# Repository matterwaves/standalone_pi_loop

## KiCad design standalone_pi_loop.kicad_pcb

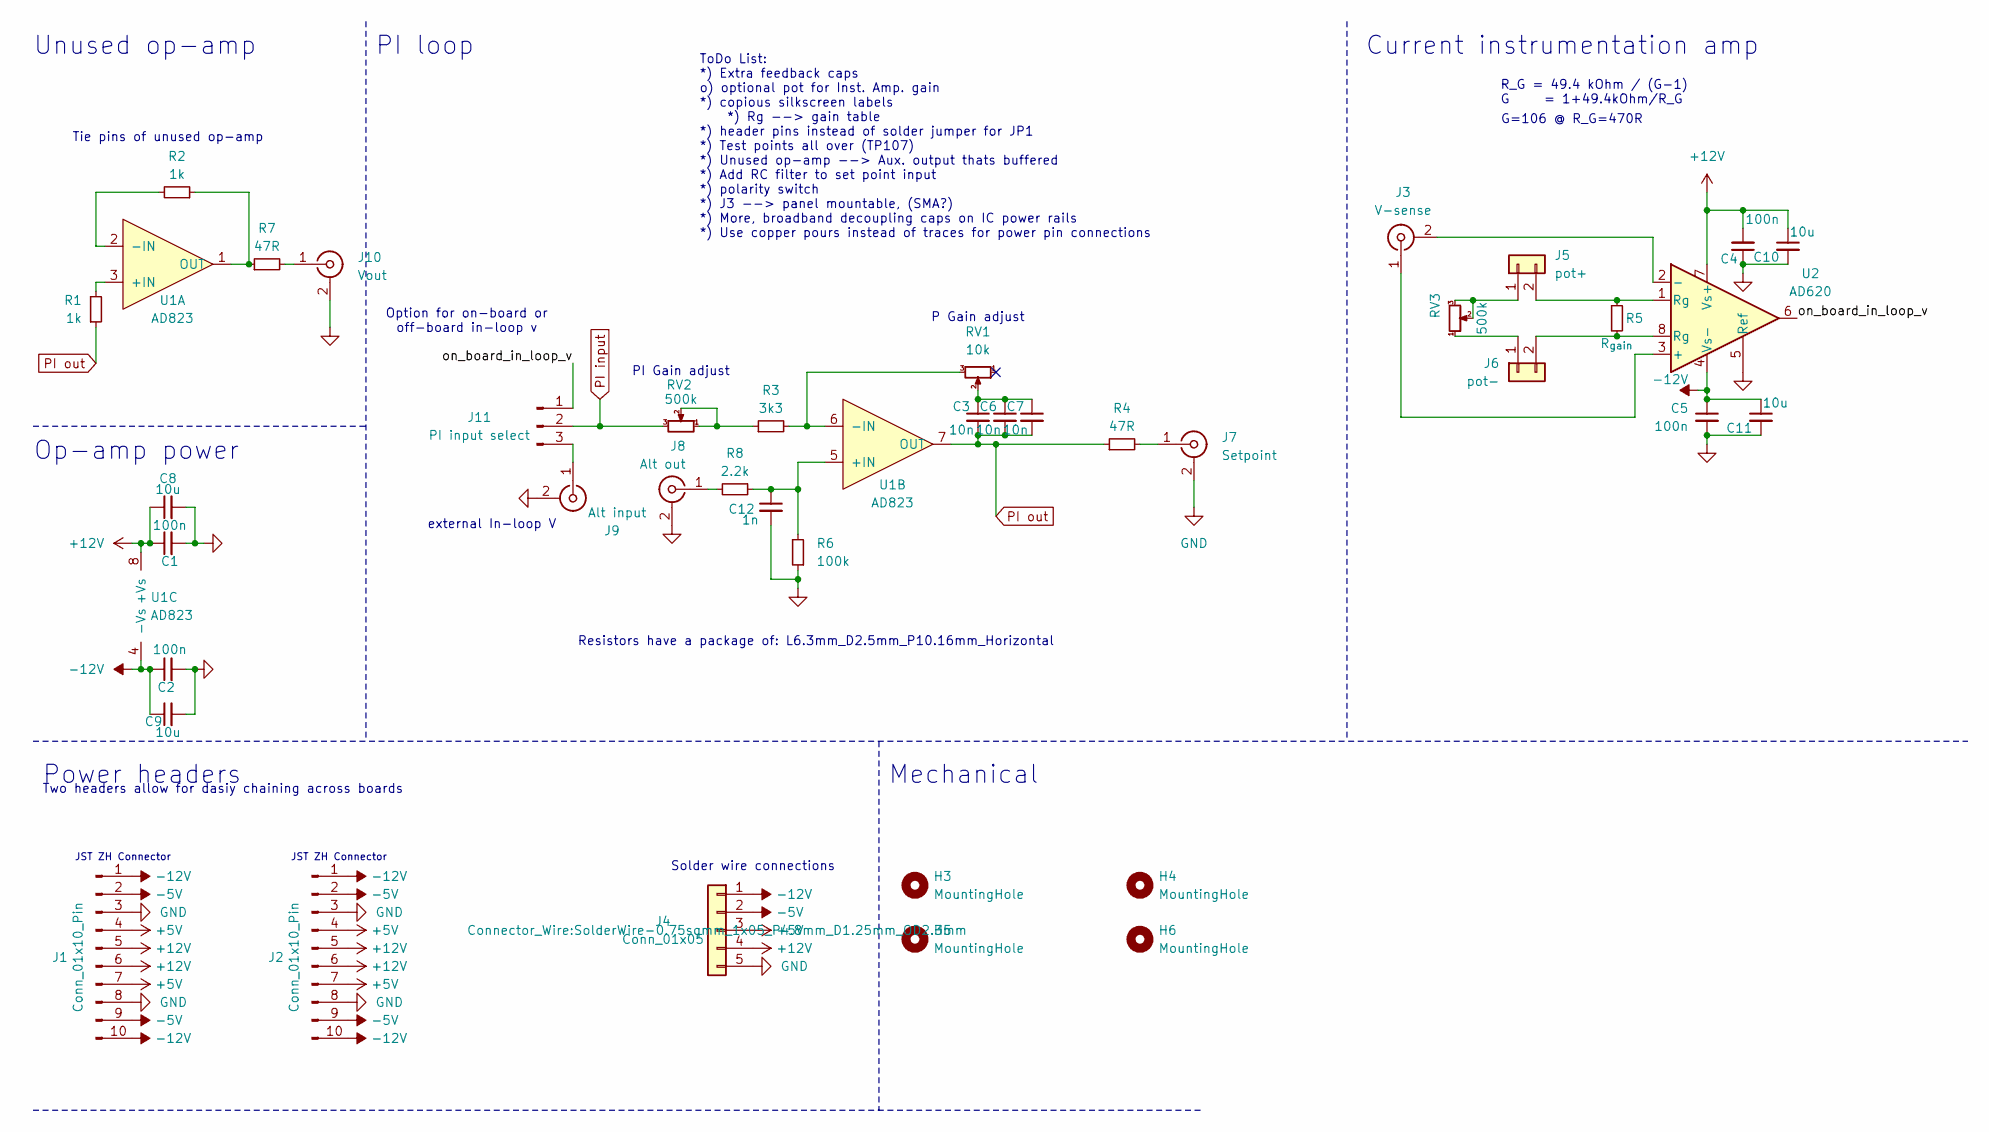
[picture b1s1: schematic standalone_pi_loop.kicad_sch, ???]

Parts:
C1, C2, C4, C5: 100n; C_Disc_D4.3mm_W1.9mm_P5.00mm
C3, C6, C7: 10n; C_Disc_D4.3mm_W1.9mm_P5.00mm
C8, C9, C10, C11: 10u; C_Disc_D4.3mm_W1.9mm_P5.00mm
C12: 1n; C_Disc_D4.3mm_W1.9mm_P5.00mm
H3, H4, H5, H6: MountingHole; MountingHole_3.2mm_M3
J1, J2: Conn_01x10_Pin; JST_ZH_B10B-ZR_1x10_P1.50mm_Vertical; Digikey PN 455-S10B-ZR-ND
J3: V-sense; SMA_Amphenol_132289_EdgeMount; Digikey PN ACX1426-ND
J4: Conn_01x05; SolderWire-0.75sqmm_1x05_P4.8mm_D1.25mm_OD2.3mm
J5: pot+; PinHeader_1x02_P2.54mm_Vertical
J6: pot-; PinHeader_1x02_P2.54mm_Vertical
J7: Setpoint; SMA_Amphenol_132289_EdgeMount; Digikey PN ACX1426-ND
J8: Alt out; SMA_Amphenol_132289_EdgeMount; Digikey PN ACX1426-ND
J9: Alt input; SMA_Amphenol_132289_EdgeMount; Digikey PN ACX1426-ND
J10: Vout; SMA_Amphenol_132289_EdgeMount; Digikey PN ACX1426-ND
J11: PI input select; PinHeader_1x03_P2.54mm_Vertical
R1, R2: 1k; R_Axial_DIN0207_L6.3mm_D2.5mm_P10.16mm_Horizontal
R3: 3k3; R_Axial_DIN0207_L6.3mm_D2.5mm_P10.16mm_Horizontal
R4, R7: 47R; R_Axial_DIN0207_L6.3mm_D2.5mm_P10.16mm_Horizontal
R5: R_{gain}; R_Axial_DIN0207_L6.3mm_D2.5mm_P10.16mm_Horizontal
R6: 100k; R_Axial_DIN0207_L6.3mm_D2.5mm_P10.16mm_Horizontal
R8: 2.2k; R_Axial_DIN0207_L6.3mm_D2.5mm_P10.16mm_Horizontal
RV1: 10k; Potentiometer_Bourns_3296W_Vertical
RV2, RV3: 500k; Potentiometer_Bourns_3296W_Vertical
U1: AD823; DIP-8_W7.62mm_Socket_LongPads
U2: AD620; DIP-8_W7.62mm_Socket_LongPads

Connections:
+5V: J1.4, J1.7, J2.4, J2.7, J4.3
+12V: C1.1, C4.2, C8.1, C10.1, J1.5, J1.6, J2.5, J2.6, J4.4, U1.8 (+Vs), U2.7 (Vs+)
-5V: J1.2, J1.9, J2.2, J2.9, J4.2
-12V: C2.1, C5.1, C9.1, C11.1, J1.1, J1.10, J2.1, J2.10, J4.1, U1.4 (-Vs), U2.4 (Vs-)
/on_board_in_loop_v: J11.1, U2.6
GND: C1.2, C2.2, C4.1, C5.2, C8.2, C9.2, C10.2, C11.2, C12.2, J1.3, J1.8, J2.3, J2.8, J4.5, J7.2 (Ext), J8.2 (Ext), J9.2 (Ext), J10.2 (Ext), R6.1, U2.5 (Ref)
unnamed: C3.1, C6.1, C7.1, RV1.2
unnamed: J3.2 (Ext), U2.2 (-)
unnamed: J3.1 (In), U2.3 (+)
unnamed: J5.1, RV3.2, RV3.3
unnamed: J5.2, R5.1, U2.1 (Rg)
unnamed: J6.1, RV3.1
unnamed: J6.2, R5.2, U2.8 (Rg)
unnamed: J7.1 (In), R4.2
unnamed: J8.1 (In), R8.2
unnamed: J10.1 (In), R7.2
unnamed: J9.1 (In), J11.3
unnamed: R3.1, RV2.1, RV2.2
unnamed: R1.2, U1.3 (+IN)
unnamed: R2.2, U1.2 (-IN)
unnamed: R2.1, R7.1, U1.1 (OUT)
unnamed: C12.1, R6.2, R8.1, U1.5 (+IN)
unnamed: R3.2, RV1.3, U1.6 (-IN)
PI input: J11.2, RV2.3
PI out: C3.2, C6.2, C7.2, R1.1, R4.1, U1.7 (OUT)

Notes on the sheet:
Solder wire connections
Resistors have a package of: L6.3mm_D2.5mm_P10.16mm_Horizontal
Current instrumentation amp
ToDo List: *) Extra feedback caps o) optional pot for Inst. Amp. gain *) copious silkscreen labels *) Rg --> gain table *) header pins instead of solder jumper for JP1 *) Test points all over (TP107) *) Unused op-amp --> Aux. output thats buffered *) Add RC filter to set point input *) polarity swi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
G=106 @ R_G=470R
PI Gain adjust
Tie pins of unused op-amp
Option for on-board or off-board in-loop v
Mechanical
JST ZH Connector
external In-loop V
Power headers
P Gain adjust
Two headers allow for dasiy chaining across boards
PI loop
Op-amp power
R_G = 49.4 kOhm / (G-1) G = 1+49.4kOhm/R_G
Unused op-amp

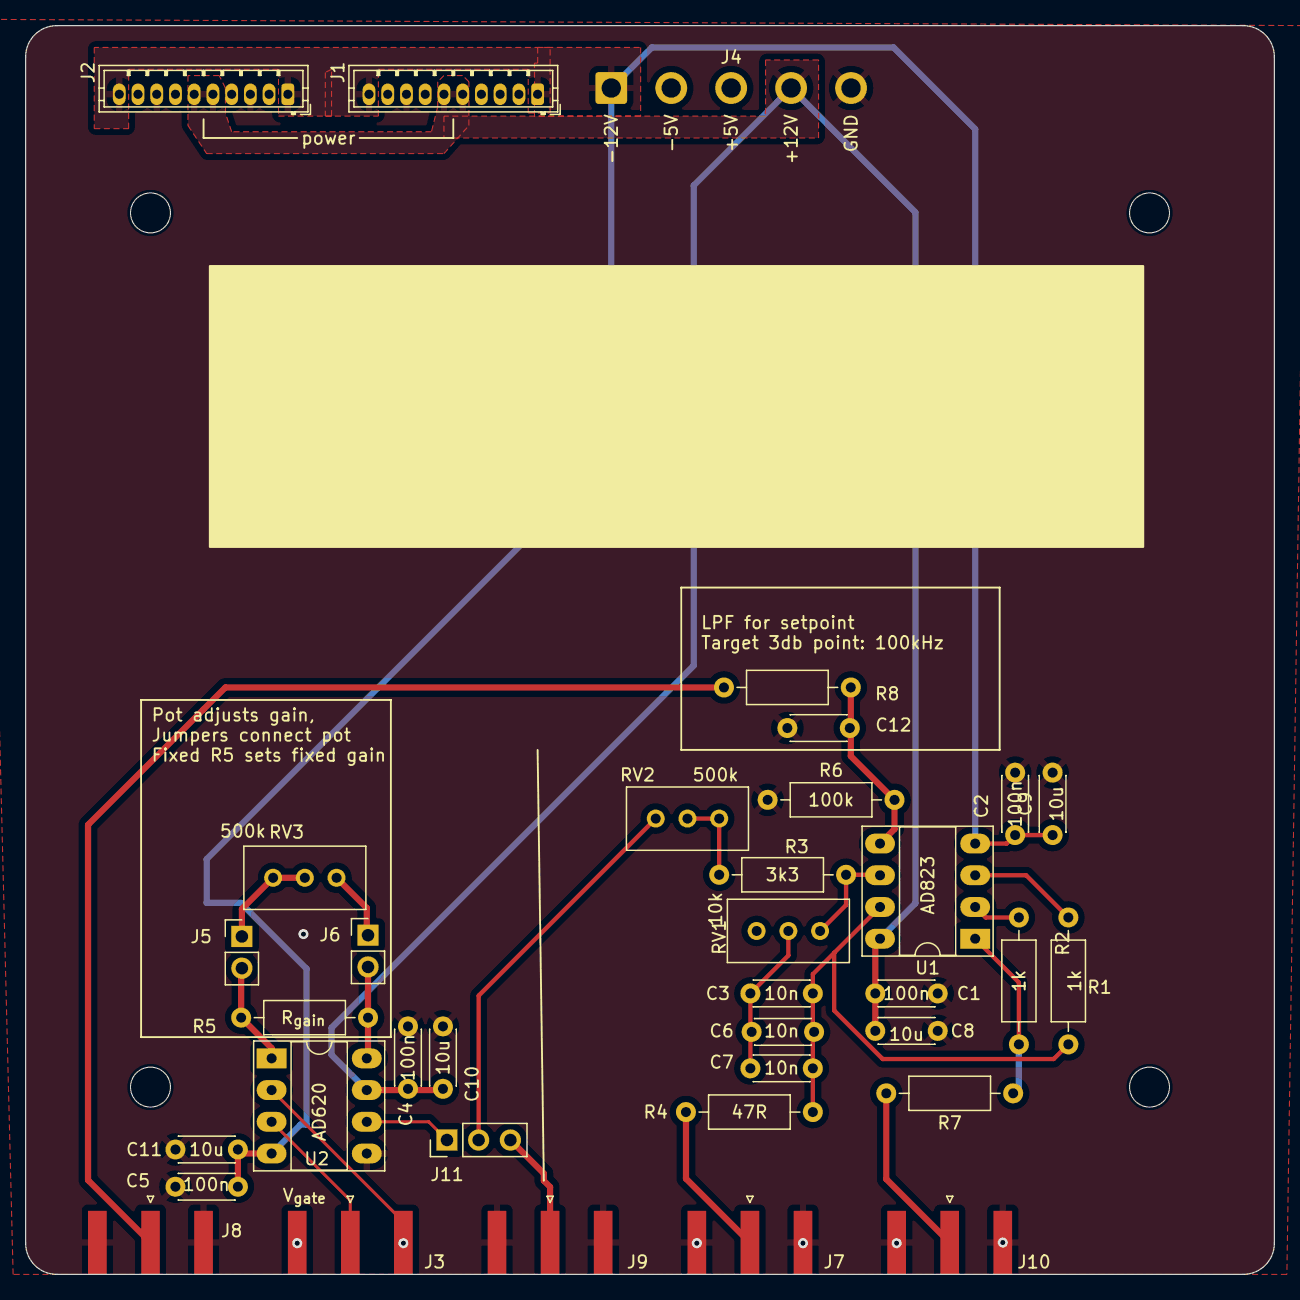
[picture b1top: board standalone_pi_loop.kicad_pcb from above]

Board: 4 copper layers, 100.0 x 100.0 mm, 40 parts (0 on the bottom side), 25 nets.

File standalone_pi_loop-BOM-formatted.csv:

Comment,Designator,Footprint,LCSC part
100n,"C1,C2,C4,C5",Capacitor_THT:C_Disc_D4.3mm_W1.9mm_P5.00mm,
10n,"C3,C6,C7",Capacitor_THT:C_Disc_D4.3mm_W1.9mm_P5.00mm,
10u,"C8,C9,C10,C11",Capacitor_THT:C_Disc_D4.3mm_W1.9mm_P5.00mm,
  ,C12,Capacitor_THT:C_Disc_D4.3mm_W1.9mm_P5.00mm,
Conn_01x10_Pin,"J1,J2",Connector_JST:JST_ZH_B10B-ZR_1x10_P1.50mm_Vertical,
V-sense,J3,Connector_Coaxial:SMA_Amphenol_132289_EdgeMount,
Conn_01x05,J4,Connector_Wire:SolderWire-0.75sqmm_1x05_P4.8mm_D1.25mm_OD2.3mm,
pot+,J5,Connector_PinHeader_2.54mm:PinHeader_1x02_P2.54mm_Vertical,
pot-,J6,Connector_PinHeader_2.54mm:PinHeader_1x02_P2.54mm_Vertical,
Setpoint,J7,Connector_Coaxial:SMA_Amphenol_132289_EdgeMount,
Alt out,J8,Connector_Coaxial:SMA_Amphenol_132289_EdgeMount,
Alt input,J9,Connector_Coaxial:SMA_Amphenol_132289_EdgeMount,
Vout,J10,Connector_Coaxial:SMA_Amphenol_132289_EdgeMount,
PI input select,J11,Connector_PinHeader_2.54mm:PinHeader_1x03_P2.54mm_Vertical,C49257
1k,"R1,R2",Resistor_THT:R_Axial_DIN0207_L6.3mm_D2.5mm_P10.16mm_Horizontal,C713997
3k3,R3,Resistor_THT:R_Axial_DIN0207_L6.3mm_D2.5mm_P10.16mm_Horizontal,C120067
47R,"R4,R7",Resistor_THT:R_Axial_DIN0207_L6.3mm_D2.5mm_P10.16mm_Horizontal,C2848560
R_{gain},R5,Resistor_THT:R_Axial_DIN0207_L6.3mm_D2.5mm_P10.16mm_Horizontal,
100k,R6,Resistor_THT:R_Axial_DIN0207_L6.3mm_D2.5mm_P10.16mm_Horizontal,C2843019
2.2k,R8,Resistor_THT:R_Axial_DIN0207_L6.3mm_D2.5mm_P10.16mm_Horizontal,C714002
10k,RV1,Potentiometer_THT:Potentiometer_Bourns_3296W_Vertical,
500k,"RV2,RV3",Potentiometer_THT:Potentiometer_Bourns_3296W_Vertical,
AD823,U1,Package_DIP:DIP-8_W7.62mm_Socket_LongPads,C5289485
AD620,U2,Package_DIP:DIP-8_W7.62mm_Socket_LongPads,C5289485

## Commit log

2024-10-16 Initial commit for standalone PI loop by Jack v1
2024-10-16 R4 -> 47R, a more common std value. added inst. amp gain formula to schematic, added PI gain adjust trimpot to schematic
2024-11-01 started schematic changes for V2, added todo list
2024-11-01 cleared all traces off PCB, ready for layout refactor
2024-11-02 Draft of layout + routing. Added alt out, LPF on setpoint.
2024-11-02 Added in power pours. Still some clean up to do.
2024-12-06 test push
2025-01-06 Date + revision added. Ready for ordering/testing
2025-01-07 Added BOM with LCSC parts and pos file for PCB ordering
2025-01-07 Created BOM and pos csv's. Added J4 in pos file
2025-01-07 Added updated gerbers for new PCB
2025-06-02 updated bypass capacitors and board design
2025-06-02 Updated schematic PDF
2025-07-04 small cosmetic changes
